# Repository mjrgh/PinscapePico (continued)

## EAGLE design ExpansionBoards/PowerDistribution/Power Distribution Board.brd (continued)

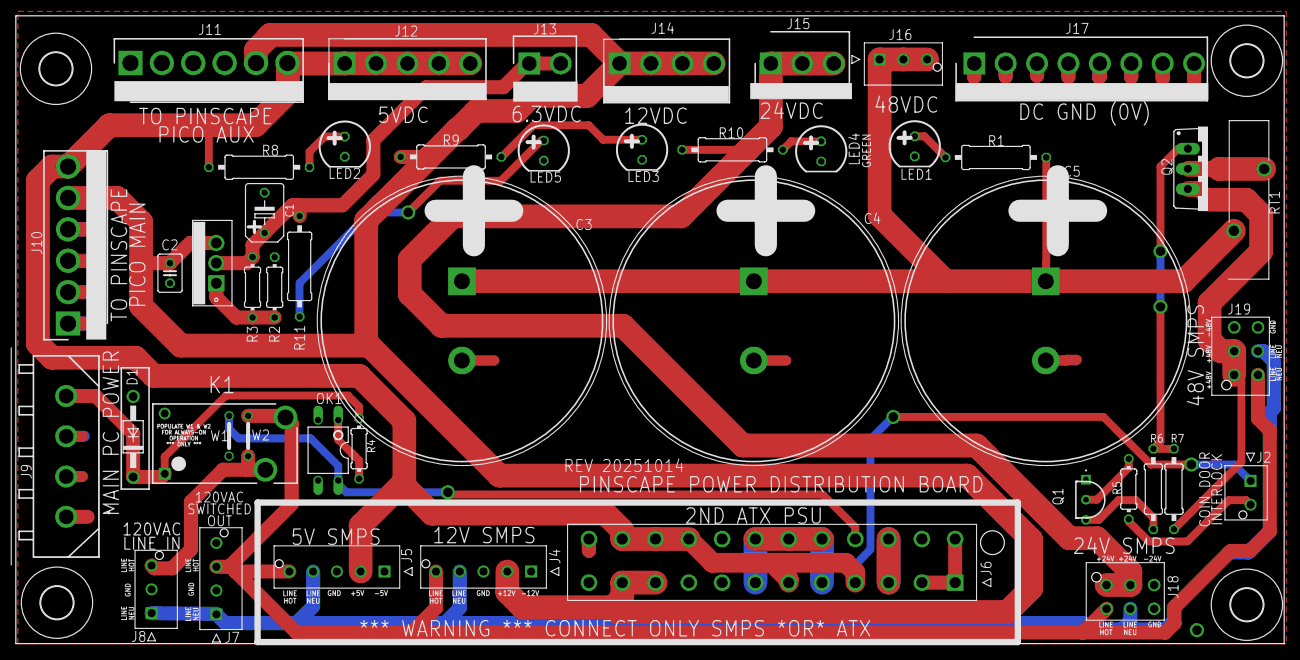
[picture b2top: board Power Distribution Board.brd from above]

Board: 2 copper layers, 160.0 x 79.2 mm, 51 parts (0 on the bottom side), 25 nets.

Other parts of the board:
U$1, U$2, U$3, U$4: 4,1

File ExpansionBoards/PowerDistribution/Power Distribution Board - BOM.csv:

Qty,Value,Parts,Description,PARTNO,Comments,ExtDescription
1,LED 5mm Blue,LED1,"LED, 5mm, blue",C503B-BCN-CV0Z0462,,"LED, 5mm, blue (LED1)"
1,0.1uF,C2,"Capacitor, ceramic, 0.1uF, radial, 2.54mm lead pitch",K104K15X7RF5TL2,,"Capacitor, ceramic, 0.1uF, radial, 2.54mm lead pitch (C2)"
1,1.1K,R2,"Resistor, 1.1K, axial, 2mm x 4mm",MFR-12FTF52-1K1,,"Resistor, 1.1K, axial, 2mm x 4mm (R2)"
1,1uF,C1,"Capacitor, Tantalum, 1uF, radial, 5mm lead pitch",TAP105K035CRS,,"Capacitor, Tantalum, 1uF, radial, 5mm lead pitch (C1)"
1,2.4K/1W,R1,"Resistor, 2.4K, 1W, axial, 3mm x 9mm",279-RR02J2K4TB,,"Resistor, 2.4K, 1W, axial, 3mm x 9mm (R1)"
1,MicroFit Hdr 2P,J2,"Molex Micro-Fit+ vertical header, 2 Ckt, black",538-216571-1002,,"Molex Micro-Fit+ vertical header, 2 Ckt, black (J2)"
1,MicroFit Plug 2P,PLUG_J2,"Molex Micro-Fit+ wire housing, 2 Ckt, black",538-215759-1002,,"Molex Micro-Fit+ wire housing, 2 Ckt, black (PLUG_J2)"
1,MicroFit Hdr 4P,J7,"Molex Micro-Fit+ vertical header, 4 Ckt, black",538-216571-1004,,"Molex Micro-Fit+ vertical header, 4 Ckt, black (J7)"
1,MicroFit Plug 4P,PLUG_J7,"Molex Micro-Fit+ wire housing, 4 Ckt, black",538-215759-1004,,"Molex Micro-Fit+ wire housing, 4 Ckt, black (PLUG_J7)"
1,MicroFit Hdr 3P,J8,"Molex Micro-Fit+ vertical header, 3 Ckt, black",538-216571-2003,,"Molex Micro-Fit+ vertical header, 3 Ckt, black (J8)"
1,MicroFit Plug 3P,PLUG_J8,"Molex Micro-Fit+ wire housing, 3 Ckt, black",538-215759-1003,,"Molex Micro-Fit+ wire housing, 3 Ckt, black (PLUG_J8)"
1,MicroFit Hdr 3P,J16,"Molex Micro-Fit+ vertical header, 3 Ckt, red",538-216571-1023,,"Molex Micro-Fit+ vertical header, 3 Ckt, red (J16)"
1,MicroFit Plug 3P,PLUG_J16,"Molex Micro-Fit+ wire housing, 3 Ckt, red",538-215759-1023,,"Molex Micro-Fit+ wire housing, 3 Ckt, red (PLUG_J16)"
1,MicroFit Hdr 5P,J1,"Molex Micro-Fit+ vertical header, 5 Ckt, black",538-216571-2005,,"Molex Micro-Fit+ vertical header, 5 Ckt, black (J1)"
1,MicroFit Plug 5P,PLUG_J1,"Molex Micro-Fit+ wire housing, 5 Ckt, black",538-215759-1005,,"Molex Micro-Fit+ wire housing, 5 Ckt, black (PLUG_J1)"
1,MicroFit Hdr 5P,J3,"Molex Micro-Fit+ vertical header, 5 Ckt, red",538-216571-1025,,"Molex Micro-Fit+ vertical header, 5 Ckt, red (J3)"
1,MicroFit Plug 5P,PLUG_J3,"Molex Micro-Fit+ wire housing, 5 Ckt, red",538-215759-1025,,"Molex Micro-Fit+ wire housing, 5 Ckt, red (PLUG_J3)"
1,MicroFit Hdr 5P,J4,"Molex Micro-Fit+ vertical header, 5 Ckt, blue",538-216571-1035,,"Molex Micro-Fit+ vertical header, 5 Ckt, blue (J4)"
1,MicroFit Plug 5P,PLUG_J4,"Molex Micro-Fit+ vertical header, 5 Ckt, blue",538-215759-1035,,"Molex Micro-Fit+ vertical header, 5 Ckt, blue (PLUG_J4)"
1,MicroFit Hdr 5P,J5,"Molex Micro-Fit+ vertical header, 5 Ckt, yellow",538-216571-1045,,"Molex Micro-Fit+ vertical header, 5 Ckt, yellow (J5)"
1,MicroFit Plug 5P,PLUG_J5,"Molex Micro-Fit+ vertical header, 5 Ckt, yellow",538-215759-1045,,"Molex Micro-Fit+ vertical header, 5 Ckt, yellow (PLUG_J5)"
35,MicroFit Crimp Pin,,"Molex Micro-Fit+ crimp pins, tin plating, 24-20 AWG",206460-0021,Select according to desired wire gauge,"Molex Micro-Fit+ crimp pins, tin plating, 24-20 AWG ()"
35,MicroFit Crimp Pin,,"Molex Micro-Fit+ crimp pins, tin plating, 18 AWG",206460-0031,Select according to desired wire gauge,"Molex Micro-Fit+ crimp pins, tin plating, 18 AWG ()"
1,Mini-Fit Jr. Hdr 24P,J6,"Molex Mini-Fit Jr. vertical header, 24 Ckt",44206-0007,,"Molex Mini-Fit Jr. vertical header, 24 Ckt (J6)"
1,1N4007,D1,"Diode, general-purpose rectifier, through-hole DO-41 package",1N4007,,"Diode, general-purpose rectifier, through-hole DO-41 package (D1)"
2,270R,"R3, R4","Resistor, 270 Ohm, axial, 2mm x 4mm",CFR25SJT-26-270R,,"Resistor, 270 Ohm, axial, 2mm x 4mm (R3, R4)"
1,350211-1,J9,"Mate-N-Lok PCB header, 4-pos straight (PC ATX floppy disk connector, male)",571-3502111,,"Mate-N-Lok PCB header, 4-pos straight (PC ATX floppy disk connector, male) (J9)"
1,571-6404452,J13,"MTA-156 pin header, 2 position",571-6404452,,"MTA-156 pin header, 2 position (J13)"
1,571-3-643819-2,PLUG_J13,"MTA-156 wire housing, IDC, 2 position, 22AWG",571-3-643819-2,,"MTA-156 wire housing, IDC, 2 position, 22AWG (PLUG_J13)"
1,571-6404453,J15,"MTA-156 pin header, 3 position",571-6404453,,"MTA-156 pin header, 3 position (J15)"
1,571-3-643819-3,PLUG_J15,"MTA-156 wire housing, IDC, 3 position, 22AWG",571-3-643819-3,,"MTA-156 wire housing, IDC, 3 position, 22AWG (PLUG_J15)"
1,571-640445-5,J12,"MTA-156 pin header, 5 position",571-640445-5,,"MTA-156 pin header, 5 position (J12)"
1,571-3-643819-5,PLUG_J12,"MTA-156 wire housing, IDC, 5 position, 22AWG",571-3-643819-5,,"MTA-156 wire housing, IDC, 5 position, 22AWG (PLUG_J12)"
1,571-640445-4,J14,"MTA-156 pin header, 4 position",571-640445-4,,"MTA-156 pin header, 4 position (J14)"
1,571-3-643819-4,PLUG_J14,"MTA-156 wire housing, IDC, 4 position, 22AWG",571-3-643819-4,,"MTA-156 wire housing, IDC, 4 position, 22AWG (PLUG_J14)"
2,571-640445-6,"J10, J11","MTA-156 pin header, 6 position",571-640445-6,,"MTA-156 pin header, 6 position (J10, J11)"
2,571-3-643819-6,"PLUG_J10, PLUG_J11","MTA-156 wire housing, IDC, 6 position, 22 AWG",571-3-643819-6,,"MTA-156 wire housing, IDC, 6 position, 22 AWG (PLUG_J10, PLUG_J11)"
1,571-640445-8,J17,"MTA-156 pin header, 8 position",571-640445-8,,"MTA-156 pin header, 8 position (J17)"
1,571-3-643819-8,PLUG_J17,"MTA-156 wire housing, IDC, 8 position, 22 AWG",571-3-643819-8,,"MTA-156 wire housing, IDC, 8 position, 22 AWG (PLUG_J17)"
1,AHQSS105DM2FA0G,K1,"Relay, 5V coil, 16A switch contacts, contact form A",523-AHQSS105DM2FA0G,,"Relay, 5V coil, 16A switch contacts, contact form A (K1)"
1,LM338T/NOPB,U3,"Voltage regulator, LM338T/NOPB",LM338T/NOPB,,"Voltage regulator, LM338T/NOPB (U3)"
1,SL22_7R010,RT1,"Inrush Current Limiter, 22mm, 7 ohms, 10A",995-SL22-7R010,,"Inrush Current Limiter, 22mm, 7 ohms, 10A (RT1)"
3,B41231B8828M000,"C3, C4, C5","Aluminum Electrolytic Capacitor, 8200uf, 63, Snap-in, 10mm lead spacing",B41231B8828M000,,"Aluminum Electrolytic Capacitor, 8200uf, 63, Snap-in, 10mm lead spacing (C3, C4, C5)"
1,2N2222A,Q1,"NPN Transistor, TO-92, 40V, 600mA, 2N2222A",637-2N2222A,,"NPN Transistor, TO-92, 40V, 600mA, 2N2222A (Q1)"
1,IRF9530,Q2,"MOSFET, P-Channel, TO-220, 100V, 14A, IRF9530",942-IRF9530NPBF,,"MOSFET, P-Channel, TO-220, 100V, 14A, IRF9530 (Q2)"
1,470R,R5,"Resistor, 470 Ohm, axial, 2mm x 4mm",CFR25SJT-52-470R,,"Resistor, 470 Ohm, axial, 2mm x 4mm (R5)"
1,8.2K 1W,R6,"Resistor, 8.2K, 1/4W, axial, 2mm x 7mm",CFR-25JT-52-8K2,,"Resistor, 8.2K, 1/4W, axial, 2mm x 7mm (R6)"
1,2.2K,R7,"Resistor, 2.2K, axial, 2mm x 4mm",CFR25SJT-26-2K2,,"Resistor, 2.2K, axial, 2mm x 4mm (R7)"
1,LTV-817,OK1,Transistor Output Optocoupler,LTV-817-A,,Transistor Output Optocoupler (OK1)
1,LED 5mm Red,LED2,"LED, 5mm, red",C503B-RAN-CZ0C0AA2,,"LED, 5mm, red (LED2)"
1,150R,R8,"Resistor, 150 Ohm, axial, 2mm x 7mm",MFR-25FTF52-150R,,"Resistor, 150 Ohm, axial, 2mm x 7mm (R8)"
1,LED 5mm Yellow,LED3,"LED, 5mm, yellow",151034YS03000,,"LED, 5mm, yellow (LED3)"
1,510R3 1/4W,R9,"Resistor, 510 Ohm, 1/4W, axial, 2mm x 7mm",MFR-25FRF52-510R,,"Resistor, 510 Ohm, 1/4W, axial, 2mm x 7mm (R9)"
1,LED 5mm Green,LED4,"LED, 5mm, green",LTL-4234,,"LED, 5mm, green (LED4)"
1,1.1K 1/2W,R10,"Resistor, 1.1K, 1/2W, axial, 2mm x 7mm",MF0207FTE52-1K1,,"Resistor, 1.1K, 1/2W, axial, 2mm x 7mm (R10)"
1,LED 5mm Orange,LED5,"LED, 5mm, orange",WP7113ED,,"LED, 5mm, orange (LED5)"
1,220R,R11,"Resistor, 220 Ohm, axial, 2mm x 7mm3",MFR50SFTE52-220R,,"Resistor, 220 Ohm, axial, 2mm x 7mm3 (R11)"

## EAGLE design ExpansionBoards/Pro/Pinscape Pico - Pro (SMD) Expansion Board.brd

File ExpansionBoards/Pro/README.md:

# Pinscape Pico "Pro" Expansion Board

This is a set of EAGLE plans for an all-in-one expansion board for
Pinscape Pico.  It includes all of the I/O ports and on-board
peripherals needed for a high-end virtual pinball cabinet, all in a
single board.

I refer to this as the "Pro" board, because it uses small-pitch SMD
parts that make it difficult to assemble by hand.  It's best suited
for robotic assembly, which probably puts it out of reach for DIY
builds.  Factory assembly of a large board like this is usually only
cost-effective when you're making at least 50 to 100 units, so I think
the only people who will want to build this board are our more
entrepreneurially-minded community members who plan to stock a batch
for retail sales.  There's a separate two-board "DIY-Friendly" set,
based entirely on through-hole parts that are easy to solder by hand,
that should be a lot more interesting if you're only planning to build
one for your own use.

## Features

* 32 button inputs, using 74HC165 shift registers for extremely
low latency

* 24 high-power MOSFET outputs with fixed-frequency (98kHz) PWM,
for devices like solenoids, motors, and basic ("dumb") LED strips

* 4 high-power MOSFET outputs with adjustable PWM frequency per port,
for devices that need special PWM frequency settings

* 15 flasher ports, 1 Amp per port, for connecting up to two flasher panels
(with 5 RGB LEDs each) in parallel, using the same ribbon cable connector
as the original Pinscape KL25Z boards; plus a 16th 1A port for a strobe
or other medium-power device

* 8 lamp ports, 500mA per port, for pushbutton lamps or other medium-power devices

* 16 small-LED ports, 120mA per port, for individual low-power LEDs

* Plunger connector compatible with the original Pinscape KL25Z expansion board plunger header,
with software support for all of the same sensors

* IR receiver and transmitter connectors, for connecting a sensor and emitter that can
be positioned anywhere inside or outside the cabinet, for line-of-sight contact
with communicating devices

* Analog input port for a two-axis potentiometer-based joystick or any other ad hoc analog inputs

* UART port for logging and console connections to the Pinscape Pico firmware

* Accelerometer (LIS3DH, but the design can be easily adapted to any other I2C accelerometer)

* High-resolution ADC (ADS1115), for improved plunger sensor input

* Real-time clock chip with con-cell battery backup, for timekeeping while the power is off

* Pinscape TV-ON power detection circuit

* Hard reset button for the Pico

## JLCPCB edition

This board is tailored to the parts catalog for JLCPCB, a Chinese PCB
fabricator that sells direct to hobbyists.  I decided to design the
board around JLCPCB's parts catalog so that I had a concrete vendor
reference point to make sure the board was actually feasible to
manufacture, with parts that could be sourced at the vendor.

There's absolutely no hard dependency on JLCPCB as the manufacturer.
Virtually every fabricator will accept the Gerber files that EAGLE can
mechanically generate from the board layout, and most fabricators can
source whatever parts you specify, one way or another.  It's just likely
to cost more and take longer if your fabricator has to order parts
separately.  If you do want to order the board from another fabricator,
you might want to go through the parts list and substitute parts that
your selected vendor keeps in stock wherever possible.  That might
require some slight customization of the board layout, of course.

## Status

This design is currently a prototype, on paper only.  I haven't
built a physical version of the whole board, although I've
physically build and tested all of the main sub subsystems to
verify that the electronic designs are sound.

All of the devices on this board are supported by the Pinscape Pico
software, and the Config Tool comes with a template configuration
file with all of the necessary settings.

## Design Notes

Some notes on choices I made in the design.

### Component selection

My original goal with the board was hand-assembly, so I started off
trying to use components that are large enough to manipulate by hand
(using tweezers, certainly, but still "by hand" as opposed to "by
robot") and that use solder-pin layouts that are feasible to assemble
with solder paste and a heat gun.  For the passive components like
resistors and capacitors, I instituted a minimum size of "1206" (which
is an electronics industry jargon term meaning 0.12" by 0.6").  I've
found that 1206 is the smallest SMD package that I can comfortably
manipulate with tweezers; it's actually quite large by modern industry
standards, but everything smaller is just too hard to work with, at
least for me.  Similarly, I tried to avoid hidden-pin IC packages like
QFN, and tried to avoid super-fine-pitch ICs below 0.5mm pitch.  Even
0.5mm pitch is tricky to solder, but it's doable with some practice.

This edition of the board doesn't stick to those limits, though.  For
this edition, I specifically targeted factory assembly, which opened
the design to smaller passive parts and other IC packages.  There are
a number of 0402 and 0603 passives, and some QFN ICs.  This allowed
improving the layout, and it also reduces the component cost of the
board, since some of the QFN parts are (for whatever reason)
significantly less costly than their SOIC versions.

### Single-sided component placement

I intentionally placed all of the components on one side of the board.
With SMD components, it's common to place components on both sides of
the board to increase density, but I avoided this because it makes
hand-assembly more difficult and typically increases the cost of
factory assembly.

### Connectors

Most of the connectors are from the TE Connectivity MTA series.  These
connectors have polarized headers, ensuring that the connector is
always inserted in the correct orientation, and the wire housings use
IDC termination with individual wires (not ribbon cables).  I wanted
to give this a try because IDC connectors are a lot quicker to
assemble then crimp-pin connectors, and they're much more reliable
than screw terminals.  I think most DIYers tend to favor screw
terminals because they don't require any special tooling or expertise
to use, but the trade-off is that they're unreliable, at least in my
experience.  I want the wiring inside my pin cab to be very robust; I
don't have to constantly troubleshoot loose connections.  I think IDC
connectors provide the best combination of reliability and quick
assembly.  However, it should be possible to replace the MTA parts
with screw terminals or crimp-pin parts.  There are Molex crimp-pin
products with the same header pin pitch as the corresponding MTA
headers.

For the plunger connector and the RGB flasher output connector, I kept
the same headers, with the same pin layouts, used in the original
Pinscape expansion boards.  This allows anyone upgrading an original
Pinscape system to just plug their existing plunger and flasher cables
into the new boards.  The one change I made vs the original boards is
that I used "shrouded" headers on this board (the original boards had
plain headers without shrouds).  The shrouded header provides a
polarizing key to ensure that the connector is inserted in the correct
orientation.

I also used shrouded 0.1" pitch, two-row pin headers for the button
inputs.  These are best with mating crimp-pin wire housings; I don't
think there are any individual-wire IDC housings available in a
two-row configuration like this, and ribbon cables aren't appropriate
here, so that leaves the crimp-pin headers.  There just isn't room for
32 buttons worth of single-row headers or screw terminals.  If you
really want screw terminals, it would be fairly easy to design a
daughter-board that would plug into the pair of 16-pin button headers,
and route the pins out to screw terminals.

The secondary power supply input is a connector that mates with the
standard floppy-disk connector on an ATX power supply.  This lets you
just plug one of the unused floppy-disk power cables from your
secondary power supply directly into the board, without having to
build the adapter cabling that was necessary with the original
expansion boards.  Hopefully that's a more convenient setup for most
people.

### Button inputs

Button inputs on the original Pinscape boards were wired directly to
GPIO ports, so each button input required one GPIO port.  That was
workable on the KL25Z, which has about 50 exposed GPIO ports, but not
on the Pico, which only exposes 26 ports.  If we could use all of the
ports for button inputs, we'd have just barely enough for the standard
pin cab complement, but that's not possible because the board has to
reserve about 16 ports for its own purposes.  That leaves only 8 ports
that could be assigned as button inputs, which clearly is too few.  We
therefore need additional hardware for the button connections.

The extra hardware used on this board is a set of four 74HC165 shift
register chips.  Each chip provides 8 input ports, so this gives us 32
button inputs total.  These chips work well for button inputs because
the Pico can scan them at extremely high speeds - it can scan the
whole set of inputs every 10 to 20 microseconds, for practically zero
latency reading the inputs.

An earlier version of this board used PCA9555 GPIO expander chips
instead of the shift registers.  The PCA9555's have a couple of nice
features compared to the shift registers: they have pull-up resistors
built in, so they don't need the 32 external resistors required in the
shift register version; and they connect to the Pico via the shared
I2C bus, so they only require one extra GPIO on the Pico (for the
PCA9555 interrupt signal line), whereas the shift register chips
require three dedicated GPIO ports.  But the PCA9555's also have a
major disadvantage, which is that I2C is quite slow.  The button scan
time with the PCA9555's is about one millisecond.  That's fast enough
for most purposes, but for a gaming device like this, it's a negative.
That's why the PCA9555 version of the board also wired four of the
button ports directly to GPIOs, so that you could at least have enough
fast ports to cover the flipper button switches.  But I think it's
nicer to have super fast scanning on all of the input ports, so that
you don't have to worry about which ports go with which buttons, thus
the change to all shift register inputs on this version of the board.

### ADC(Analog-to-Digital Converter)

The board has a dedicated ADC chip for quantizing analog voltage input
from a plunger device.  The Pico has its own on-board ADC, but the
Pico's ADC isn't a very good one; it has low resolution and some known
deficiencies.  The most popular plunger sensor type right now is
probably the linear potentiometer, and those benefit greatly from
high-resolution quantization, so I thought it was worth including a
good ADC in the design.

### PWM chips and MOSFET gate drivers

The PWM controllers on this board are TI's TLC59116F, which are
16-channel I2C chips with open-drain outputs that can sink 120mA per
channel.  Note that the "F" suffix is critical here!  TI also sells a
very similar part without the "F" suffix that has constant-current
outputs.  This board requires the open-drain version.

The TLC59116F replaces the TLC5940NT used in the original Pinscape
boards.  This chip has a couple of advantages.  One is that it has a
standard I2C bus interface for the microcontroller connection, which
only requires two GPIO ports on the Pico and is easier to work with
(from the software's perspective) than the older chip's ad hoc serial
interface.  The other is that it has a much higher PWM frequency than
the older chip, at 97kHz.  The high frequency is useful because it's
well above the human hearing range, which makes the PWM signal
inaudible if a PWM-controlled device transduces the PWM signal to
mechanical vibration.  Some devices, particular motors and large
solenoids, tend to vibrate at the PWM frequency when controlled with
PWM.  If the PWM frequency is in the human hearing range (40Hz to at
most 20kHz, depending on the individual), the vibration manifests as
audible noise.  It can be difficult or impossible to get rid of the
vibration with mechanical treatments, so the only workable solution in
many cases is to increase the PWM frequency above 20kHz, so that the
noise is too high-pitched for humans to hear.  The older TLC5940NT
chips couldn't run at high enough frequencies to get out of the
audible range, but the TLC59116F's native 97kHz frequency is safely
out of human range.  It's probably even high enough that it won't
annoy your dog.

The MOSFET outputs are connected to the PWM chips through TI's
UCC27523 gate driver chips.  The UCC27523 is an inverting gate driver
with an internal pull-up, which means that an unconnected or floating
input is pulled high (by the internal resistor) and places the MOSFET
in an OFF state, whereas an input line that's pulled to ground places
the MOSFET in an ON state.  This mates perfectly with the TLC59116F's
open-drain outputs, which are floating when the PWM signal is OFF and
pulled to ground when the PWM signal is ON.  On the MOSFET side, the
UCC27523 provides a high-current push-pull input to the MOSFET gate,
which rapidly charges or discharges the gate at each state change.
The chips are capable of driving the gate at up to 1A, which lets them
charge and discharge high-gate-capacitance MOSFETs at high switching
speeds.  The board uses 12V for the gate drive power supply, which is
compatible with most power MOSFETs in the voltage/current range we
need.  This allows for a very wide range of MOSFETs to be used, since
we don't have to be at all picky about Vgs(th) or gate capacitance.
Board builders can choose MOSFETs based largely on price; just filter
by your minimum Vds and Id needs.

The gate driver chips have the additional benefit that they're
designed for glitch-free startup, which should prevent the annoying
random solenoid firing that sometimes happened with the original
Pinscape boards.

The original Pinscape boards used optocouplers to serve the same
function of inverting the PWM signal to drive the MOSFET gates.  The
UCC27523 chips are a far superior solution, for several reasons.  The
first is that most optocouplers can't switch fast enough to keep up
with the TLC59116F's 97kHz PWM signal, so intensity adjustments
wouldn't pass through reliably to attached devices.  The second is
that optocouplers can't deliver enough current to the MOSFET gate for
efficient switching, which means the MOSFET can heat excessively
because it's spending too much time in a high-resistance state.  Many
larger power MOSFETs have a relatively high gate capacitance that
requires high current on the gate drive to achieve fast enough
switching to avoid excess heating.  The gate driver chips are
specifically designed to deliver high current to the gate for cool
operation.  A bonus feature is that the gate driver chips take up less
space on the board than most optocouplers, which made it possible to
pack more MOSFET output ports onto the board.

### Glitch-free and lockup-free output design

The design has several elements meant to guarantee that the output
ports are free of startup and shutdown glitches (meaning that all of
the output ports consistently OFF when the board is powered on, and
turn off again immediately while the board is being powered down).  I
also tried to ensure that ports designated as solenoid ports can never
lock on due to a software fault, on either the PC or in the Pico
firmware.

Glitch-free startup and shutdown are the hardware's responsibility.
The whole issue here is that there's a brief period at each end of a
power cycle where the software isn't running, because the MCU is
deliberately not executing any software instructions while the voltage
supply is rising or falling.  During these periods, the software can't
send commands to the output controller chips to tell them to disable
the outputs, so the hardware has to be designed in such a way that
everything is deterministically in an OFF state at power-on and again
whenever the MCU is in a reset state.

The TLC59116 chips provide guaranteed glitch-free startup and shutdown
at their output ports (they use an internal power-on reset circuit
that holds the outputs in the OFF state while the supply voltage is
below a threshold).  The small LEDs are directly connected to the
TLC59116 outputs, so those get glitch-free startup by virtue of the
TLC59116's glitch-free startup.  The Darlington outputs and MOSFET
outputs are all triggered through inverters with pulled-up inputs, so
they'll remain OFF whenever their TLC59116 ports are OFF.

Guaranteeing that ports won't lock up due to a software fault is a
separate matter.  Power-on glitching is annoying but rarely does any
damage; locked-up outputs can actually break things.  Pinball coils
such as knockers, and similar large solenoids, are designed for brief
activation only, and will overheat and fail (the coil wire will act
like a fuse and simply melt) if power is applied continuously for more
than a few seconds at a time.  There are two scenarios in a virtual
pinball setup where software faults can leave ports locked on.  The
first is that the application software on the PC crashes or freezes,
or is simply programmed incorrectly, in such a way that it turns an
output port ON and then fails to turn it back OFF soon enough to avoid
damage to the connected device.  USB disconnects and glitches are in
this same class of failures, in that they could prevent the PC from
sending a required OFF command.  The second failure mode is that the
MCU firmware crashes or freezes, which makes it stop responding to
commands from the PC.  If a port is ON at the moment of a crash, the
crashed MCU firmware won't be able to obey the OFF command from the
PC, even if everything on the PC side is still working properly.

The original Pinscape boards took a very hardware-centric approach to
this problem, by providing hardware timers on certain ports (the
knocker port on the main board and all ports on the Chime board).  The
hardware timers were designed so that the port was actually
"edge-sensitive" rather than "level-sensitive": the port only turned
on at a low-to-high transition from the MCU output, and then only
turned on for a fixed time period.  So if the MCU turned a port ON and
then held it on continuously, the timed port would only stay on for
the hardware-programmed interval, and wouldn't turn on again until a
new low-to-high transition on the MCU port.  This approach inherently
addressed every possible software fault up and down the entire
software stack, because the only thing that mattered was the final
port signal coming out of the MCU.  If the final port signal got stuck
ON, for whatever reason, the port would still turn off thanks to the
hardware timer.

This design doesn't have the hardware timers.  They add a lot of
complexity and extra parts, and I decided we could get the same level
of reliability without them.  The hardware timers also weren't
configurable - a port was either a timer-protected port or it wasn't.
Doing everything in software lets you designate any port for timer
protection, and also allows for variations on the behavior, such as
adjusting the timer interval, and having the option to switch a port
to a low-power mode after the timeout (the "flipper logic" scheme in
the original Pinscape software) instead of cutting power entirely.

The new design has three layers of protection.  These are truly
layers, in that each one is an independent backup for the next.  The
first layer is the Flipper Logic/Chime Logic software control, which
applies the same principle as the original hardware timer, but
implemented in the firmware software instead of in dedicated hardware
on the board.  This is the weakest link in terms of the "guarantee",
since it depends upon the firmware correctly executing the timer
behavior as configured.  My own estimation is that the timer logic
itself is simple enough that it can be made highly reliable IN
ISOLATION - meaning that we can rely on it to function properly AS
LONG AS the firmware OVERALL is still running properly.  The main
risk, in other words, isn't that the timer logic would screw up, but
that a bug in some unrelated part of the software would cause the
whole firmware program to crash or freeze or get stuck doing some
unrelated task, preventing the part of the code that operates the
timer from executing properly or in a timely fashion.

That's where the second layer of protection comes in.  The second
layer is the Pico's "watchdog".  This is a hardware subsystem on the
Pico that runs a hardware countdown timer that reboots the Pico after
a software-configured interval expires, UNLESS the software intervenes
to prevent the reboot.  This is a widely used technique in embedded
systems, and it's highly effective, because it provides a
hardware-level guarantee that the system will reset if the software
doesn't behave "as expected", where the expectation is that the
software must, in essence, tell the watchdog "I'm still working" at
regular intervals.  For this application, the interval in question
simply has to be shorter than the time it would take for lock-up
condition to damage an attached pinball coil.  This is within entirely
reasonable bounds - it takes a couple of seconds of lock-up to burn
out most coils, and the firmware main loop is on the order of
milliseconds.  So setting the watchdog interval to something on the
order of 10 to 100 milliseconds would catch lock-ups well before they
could do any damage.  It's still important to design the software
carefully; in particular, since the most important purpose of the
watchdog by far is to prevent output port lock-up, the watchdog "I'm
still alive" signaling should be closely coupled to the code that
executes the port protection timers.

The third layer of protection is similar to the power-on glitch
protection, but in this case it applies to the MCU RESET condition
rather than power supply transitions.  This layer is necessarily at
the hardware level, since it has to deal with the aftermath of a
software fault that caused the Pico watchdog to intervene by resetting
the Pico.  The goal here is to ensure that all of the output ports are
immediately and deterministically turned OFF when the Pico enters
RESET state, and deterministically stay off until the software
restarts and takes control of the ports again.  We can accomplish this
fairly easily by taking advantage of a hardware feature of the Pico,
and a hardware feature of the TLC59116 chips.  When the Pico is in the
RESET state, it configures all of its GPIO ports as "inputs", which
places them in a high-impedance state (essentially an open-drain
connection).  The input/high-impedance configuration remains in effect
until the software explicitly changes the GPIO to some other mode, so
this is the state from the moment a RESET occurs until the software is
fully in control again.  So let's start by designating one Pico GPIO
as the /OUTPUT_RESET signal, and tying this GPIO to GND through a
pull-down resistor.  The pull-down assures that this signal will be at
GND through a Pico reset, and remain at GND until the software
explicitly programs the port as an output and drives it high.  We can
then tie this /OUTPUT_RESET signal to the /RESET input pin on each of
the TLC59116 chips.  Holding this line low on a TLC59116 forces all of
the chip's output ports to their OFF state, exactly as during the
power-on/power-off supply voltage transitions.  This ensures that the
connected small LED, Darlington, and MOSFET ports are all off, for the
reasons discussed above.  When the CPU completes its RESET cycling, it
will restart the firmware, which will in turn initialize its
connections to the TLC59116 chips.  Part of this initialization will
be to drive the /OUTPUT_RESET line high to allow the TLC59116 chips to
come out of their reset state.  When they do, they're designed to hold
all of the outputs OFF until the host explicitly sets them to another
state, so we have a smooth transition back into normal operation, with
all ports turned OFF and held OFF until the software is properly
running again.

### Darlington outputs and small LED outputs

Like the original Pinscape boards, this board has a mix of MOSFET
outputs, Darlington outputs, and direct PWM-chip outputs.  All of the
ports work the same way from the user's perspective: they're all
low-side switches that serve as the "ground" connection for one device
each.  The only difference between the port types is the amount of
power that each port can handle.  Ideally, every port would be a
MOSFET port, because those are the most general-purpose port, capable
of handling any type of device from low power to high power.  Cab
builders wouldn't have to worry about using special port types per
device because every port would work with any device.  The reason we
*didn't* use all MOSFET ports is that it would take up too much space
on the board.  A MOSFET port takes up about twice the amount of space
of a Darlington port, which in turn takes up perhaps 4X the space of a
small LED port.  The mixture of port types makes it possible to
include enough ports to connect all of the common virtual pinball
devices without making the circuit board gigantic (and prohibitively
expensive).

The theory of operation of the MOSFET ports was described earlier.
The Darlington ports work similarly, but Darlingtons don't need the
gate driver chips, since they trigger on a small current on the
transistor base.  Instead, we use a small pre-biased PNP transistor on
each port to act as a logic inverter to convert the TLC59116F's
open-drain output logic to a positive voltage source on the Darlington
base input.  The Pinscape boards used optocouplers to serve the same
purpose for their Darlington outputs; the PNP inverters in this design
take up less space and switch faster than typical optocouplers, which
(as mentioned in the MOSFET section above) is necessary to handle the
TLC59116F's high PWM frequency.  The pre-biased PNP transistors are
available in "array" packages that have two transistor (and the
associated bias transistors) per package, which further improves board
density and assembly workload.

The direct PWM output ports for small LEDs work almost exactly the
same way as in the original Pinscape board.  These output ports on the
board are simply wired directly to the corresponding TLC59116F ports,
without any booster circuitry, which means they can sink up to the
maximum current that the TLC59116F chip itself can handle, which is
120mA per port (which is ample for virtually any small LED).  The only
difference from the original Pinscape boards is that these chips are
simple open-drain current sinks, whereas the original boards had
constant-current sinks.  On this board, therefore, the external LED
circuit must include a current-limiting resistor.  I think this is an
improvement over the constant-current ports on the original Pinscape
boards, since it's much easier to use with a heterogeneous set of
LEDs.  The constant-current sink on the original boards was convenient
in that you didn't need to include current-limiting resistors, but the
requirement to choose a fixed current level was too inflexible.

### IR Remote

This board has support for an optional IR remote control transmitter
and receiver.  You can connect either or both as desired.  The IR
transmitter lets you send commands to your TVs and any other devices
that can receive IR signals, which you can use to send them commands
to power on, select inputs or video modes, etc.  The IR receiver lets
Pinscape receive IR remote control codes from just about any IR remote
control you have handy.  You can use IR remote inputs as though they
were physical buttons on the cabinet, to send commands to the PC host.

Both the transmitter and receiver are designed to be separated from
the main board, so that you can place them in convenient locations
where transmitters and receivers can "see" each other properly.  This
lets the signals get in and out even if the main board is buried deep
inside your pinball cabinet.  The off-board devices connect to
the main board through cables, which connect to headers on the main
board (the headers labeled IR-TX, for the transmitter, and IR-RX, for
the receiver).

<b>Transmitter:</b>  The IR transmitter is located off of the main
board, but it doesn't require its own separate circuit board, because
the whole receiver consists of just a single small LED.  You simply
solder wires directly to the LED and run them back to the main
board.  See the [IR-TX](../IR-TX/) folder for help with wiring the IR LED.
After wiring the LED, plug it into the IR-TX header on the main board.

Note that the BOM lists two options for the IR LED: VSLB4940 and
TSAL6400.  You only need one or the other, and they're
interchangeable, so you can pick whichever one is cheaper or more
readily available.  No changes are required to the expansion board.
Other things being equal, I'd go with VSLB4940, because it has
slightly better luminosity specs, which should give it slightly better
range.

<b>Receiver:</b> The receiver requires a small "satellite" circuit
board, because the sensor that does the receiving has a couple of
extra supporting parts that have to be installed alongside it.  See the
[IR-RX](../IR-RX/) folder for the receiver circuit board design.  After building the
board and wiring the cable, plug the cable into the IR-RX header on
the main board.

### Power sensing circuit

This board uses a redesigned power-sensing circuit.  It serves the
same function as the power-sensing circuit on the original Pinscape
boards, and has a similar theory of operation, but I revamped the
electronic design using a couple of special-purpose IC chips rather
than the discrete component design of the original boards.

The original circuit is essentially a flip-flop that resets to a logic
'0' state each time the secondary power supply (PSU2) powers up.  The
microcontroller (KL25Z on the old board, Pico on the new board) reads
the flip-flop state through an optocoupler, which isolates the MCU's
power supply from the secondary supply.  The isolation is critical
because the whole point of the circuit is to let the MCU detect when
power has been cycled on the secondary supply even if the MCU itself
is continuously powered at all times through the USB port, which is
usually the case due to the PC being on a "soft power" control rather
than actually having its AC power cord unplugged between sessions.
The MCU can also attempt to *set* the flip-flop state through a second
optocoupler.  When the flip-reads as logic '0', it means that either
PSU2 is off (so it can't power the optocoupler, causing it to read as
a zero voltage and thus logic '0') *or* that the flip-flop has been
reset (cleared to logic '0') by a power cycle on PSU2 (recall that the
circuit is designed so that the flip-flop is always cleared after a
power cycle).  The MCU can distinguish the two cases by attempting to
set the flip-flop, and then reading back the result; if the flip-flop
reads as logic '1' after the set operation, the flip-flop must have
power, so the fact that it read as '0' previously means that PSU2 has
been turned back on after a period of being off.  This state change is
what triggers the TV-ON timer because it means that the cab has just
been powered up and is in the process of initializing.  If the
flip-flop still reads as '0' after a set operation, it means that PSU2
is currently off, so the MCU should do nothing for now and simply
check back later.

The old design used a couple of transistors to implement the
flip-flop.  The new design uses a flip-flop IC instead.  Since
flip-flop ICs power on in an indeterminate state, we also use a "POR"
(Power-On Reset) IC to force the flip-flop into a logic '0' state when
PSU2 powers on.  The POR chip is a special-purpose chip designed to
assert a RESET signal for a predictable interval after the power
supply stabilizes above a threshold voltage after being below the
threshold (typically meaning that power was off for a time).  The
combination of the flip-flop and POR chip (plus the pair of
optocouplers from the original design) implements exactly the behavior
we need.  The reason for the redesign is that it uses fewer
components, reducing cost and assembly workload, and accomplishes the
design goals more robustly.  The flip-flop and POR chips are designed
for these specific tasks, and are engineered to much higher standards
than my ad hoc design.

### 6.3VDC power supply

An early version of the board included a 6.3V regulator to supply
power for commonly used small pinball lamps (#555, #44, etc), used in
coin doors (for the coin chute lamps) and Suzo-Happ lighted
push-buttons.  This was eliminated in later versions (due to space
constraints).  However, there's a companion Power Distribution Board
that includes the same 6.3V regulator.

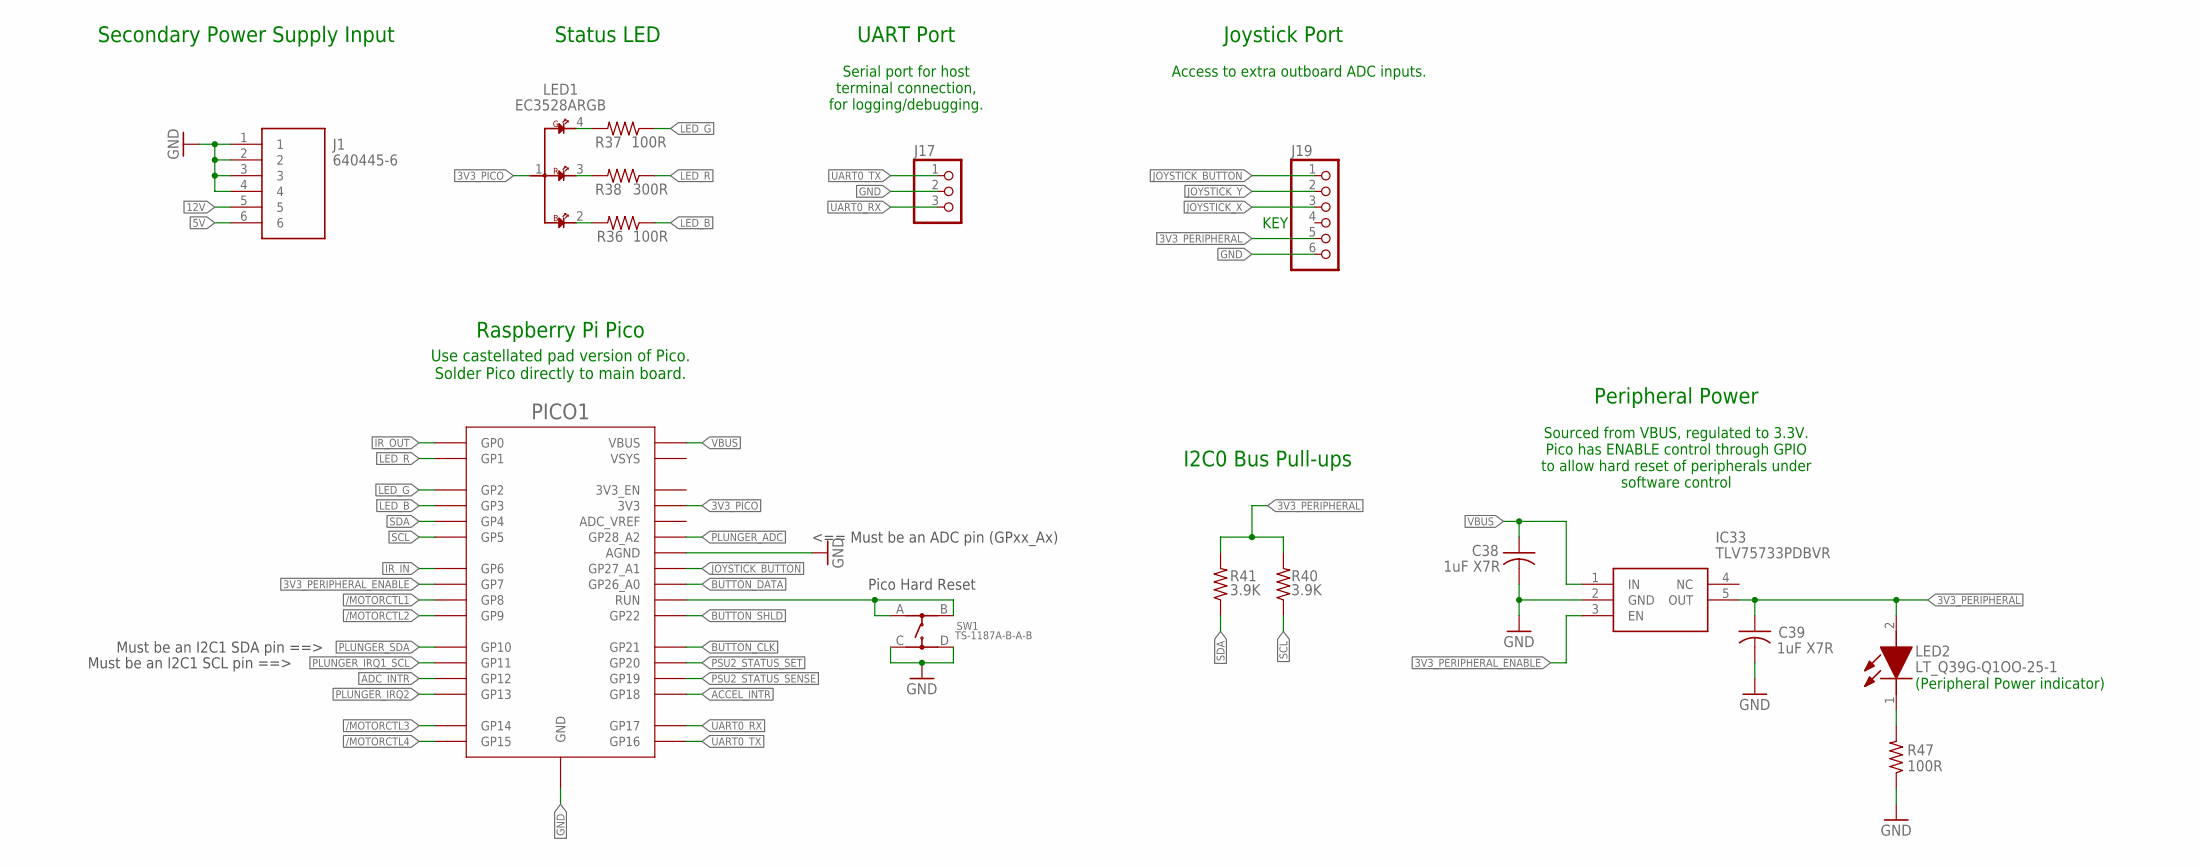
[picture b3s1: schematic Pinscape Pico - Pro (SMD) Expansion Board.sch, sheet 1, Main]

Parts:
C38, C39: 1uF X7R; C1206
IC33: TLV75733PDBVR; SOT95P280X145-5N
J1: 640445-6; SHDR6W183P0X396_1X6_2377X762X1
J17: PINHD-1X3; 1X03
J19: PINHD-1X6; 1X06
LED1: EC3528ARGB
LED2: LT_Q39G-Q1OO-25-1; LEDC1608X40N
PICO1: PICO; RPI_PICO_TH_NO_DEBUG
R36, R37, R47: 100R; R0402
R38: 300R; R0402
R40, R41: 3.9K; R0603
SW1: TS-1187A-B-A-B

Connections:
3V3_PERIPHERAL: C39.1, IC33.5 (OUT), J19.5, LED2.2 (A), R40.2, R41.2; also elsewhere on the board
3V3_PERIPHERAL_ENABLE: IC33.3 (EN), PICO1.GP7
3V3_PICO: LED1.1, PICO1.3V3; also elsewhere on the board
5V: J1.6; also elsewhere on the board
12V: J1.5; also elsewhere on the board
/MOTORCTL1: PICO1.GP8; also elsewhere on the board
/MOTORCTL2: PICO1.GP9; also elsewhere on the board
/MOTORCTL3: PICO1.GP14; also elsewhere on the board
/MOTORCTL4: PICO1.GP15; also elsewhere on the board
ACCEL_INTR: PICO1.GP18; also elsewhere on the board
ADC_INTR: PICO1.GP12; also elsewhere on the board
BUTTON_CLK: PICO1.GP21; also elsewhere on the board
BUTTON_DATA: PICO1.GP26_A0; also elsewhere on the board
BUTTON_SHLD: PICO1.GP22; also elsewhere on the board
GND: C38.2, C39.2, IC33.2 (GND), J1.1, J1.2, J1.3, J1.4, J17.2, J19.6, PICO1.AGND, PICO1.GND@1 (GND), PICO1.GND@2 (GND), PICO1.GND@3 (GND), PICO1.GND@4 (GND), PICO1.GND@6 (GND), PICO1.GND@7 (GND), PICO1.GND@8 (GND), R47.1, SW1.C, SW1.D; also elsewhere on the board
IR_IN: PICO1.GP6; also elsewhere on the board
IR_OUT: PICO1.GP0; also elsewhere on the board
JOYSTICK_BUTTON: J19.1, PICO1.GP27_A1
JOYSTICK_X: J19.3; also elsewhere on the board
JOYSTICK_Y: J19.2; also elsewhere on the board
LED_B: PICO1.GP3, R36.1
LED_G: PICO1.GP2, R37.1
LED_R: PICO1.GP1, R38.1
unnamed: LED1.3, R38.2
unnamed: LED1.2, R36.2
unnamed: LED1.4, R37.2
unnamed: PICO1.RUN, SW1.A, SW1.B
unnamed: LED2.1 (K), R47.2
PLUNGER_ADC: PICO1.GP28_A2; also elsewhere on the board
PLUNGER_IRQ1_SCL: PICO1.GP11; also elsewhere on the board
PLUNGER_IRQ2: PICO1.GP13; also elsewhere on the board
PLUNGER_SDA: PICO1.GP10; also elsewhere on the board
PSU2_STATUS_SENSE: PICO1.GP19; also elsewhere on the board
PSU2_STATUS_SET: PICO1.GP20; also elsewhere on the board
SCL: PICO1.GP5, R40.1; also elsewhere on the board
SDA: PICO1.GP4, R41.1; also elsewhere on the board
UART0_RX: J17.3, PICO1.GP17
UART0_TX: J17.1, PICO1.GP16
VBUS: C38.1, IC33.1 (IN), PICO1.VBUS

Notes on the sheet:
Secondary Power Supply Input
I2C0 Bus Pull-ups
Status LED
Raspberry Pi Pico
Use castellated pad version of Pico. Solder Pico directly to main board.
Must be an I2C1 SCL pin ==>
<== Must be an ADC pin (GPxx_Ax)
Must be an I2C1 SDA pin ==>
Pico Hard Reset
UART Port
Serial port for host terminal connection, for logging/debugging.
Joystick Port
Access to extra outboard ADC inputs.
KEY
Peripheral Power
Sourced from VBUS, regulated to 3.3V. Pico has ENABLE control through GPIO to allow hard reset of peripherals under software control
(Peripheral Power indicator)

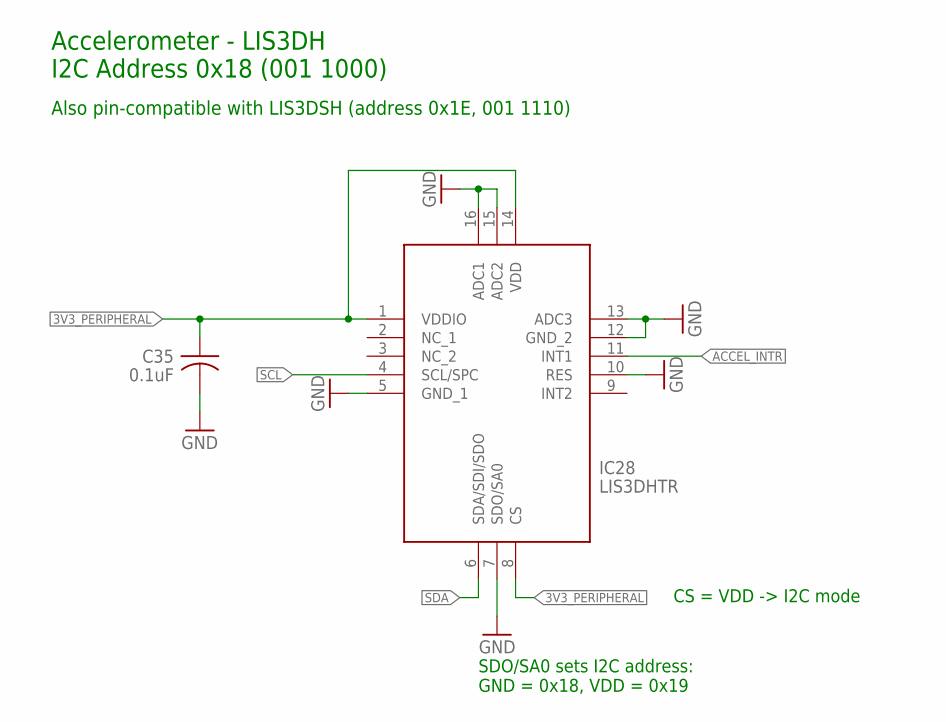
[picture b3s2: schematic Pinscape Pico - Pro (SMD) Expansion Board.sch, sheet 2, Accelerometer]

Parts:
C35: 0.1uF; C0402
IC28: LIS3DHTR

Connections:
3V3_PERIPHERAL: C35.1, IC28.1 (VDDIO), IC28.8 (CS), IC28.14 (VDD); also elsewhere on the board
ACCEL_INTR: IC28.11 (INT1); also elsewhere on the board
GND: C35.2, IC28.5 (GND_1), IC28.7 (SDO/SA0), IC28.10 (RES), IC28.12 (GND_2), IC28.13 (ADC3), IC28.15 (ADC2), IC28.16 (ADC1); also elsewhere on the board
SCL: IC28.4 (SCL/SPC); also elsewhere on the board
SDA: IC28.6 (SDA/SDI/SDO); also elsewhere on the board

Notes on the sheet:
Accelerometer - LIS3DH I2C Address 0x18 (001 1000)
SDO/SA0 sets I2C address: GND = 0x18, VDD = 0x19
CS = VDD -> I2C mode
Also pin-compatible with LIS3DSH (address 0x1E, 001 1110)

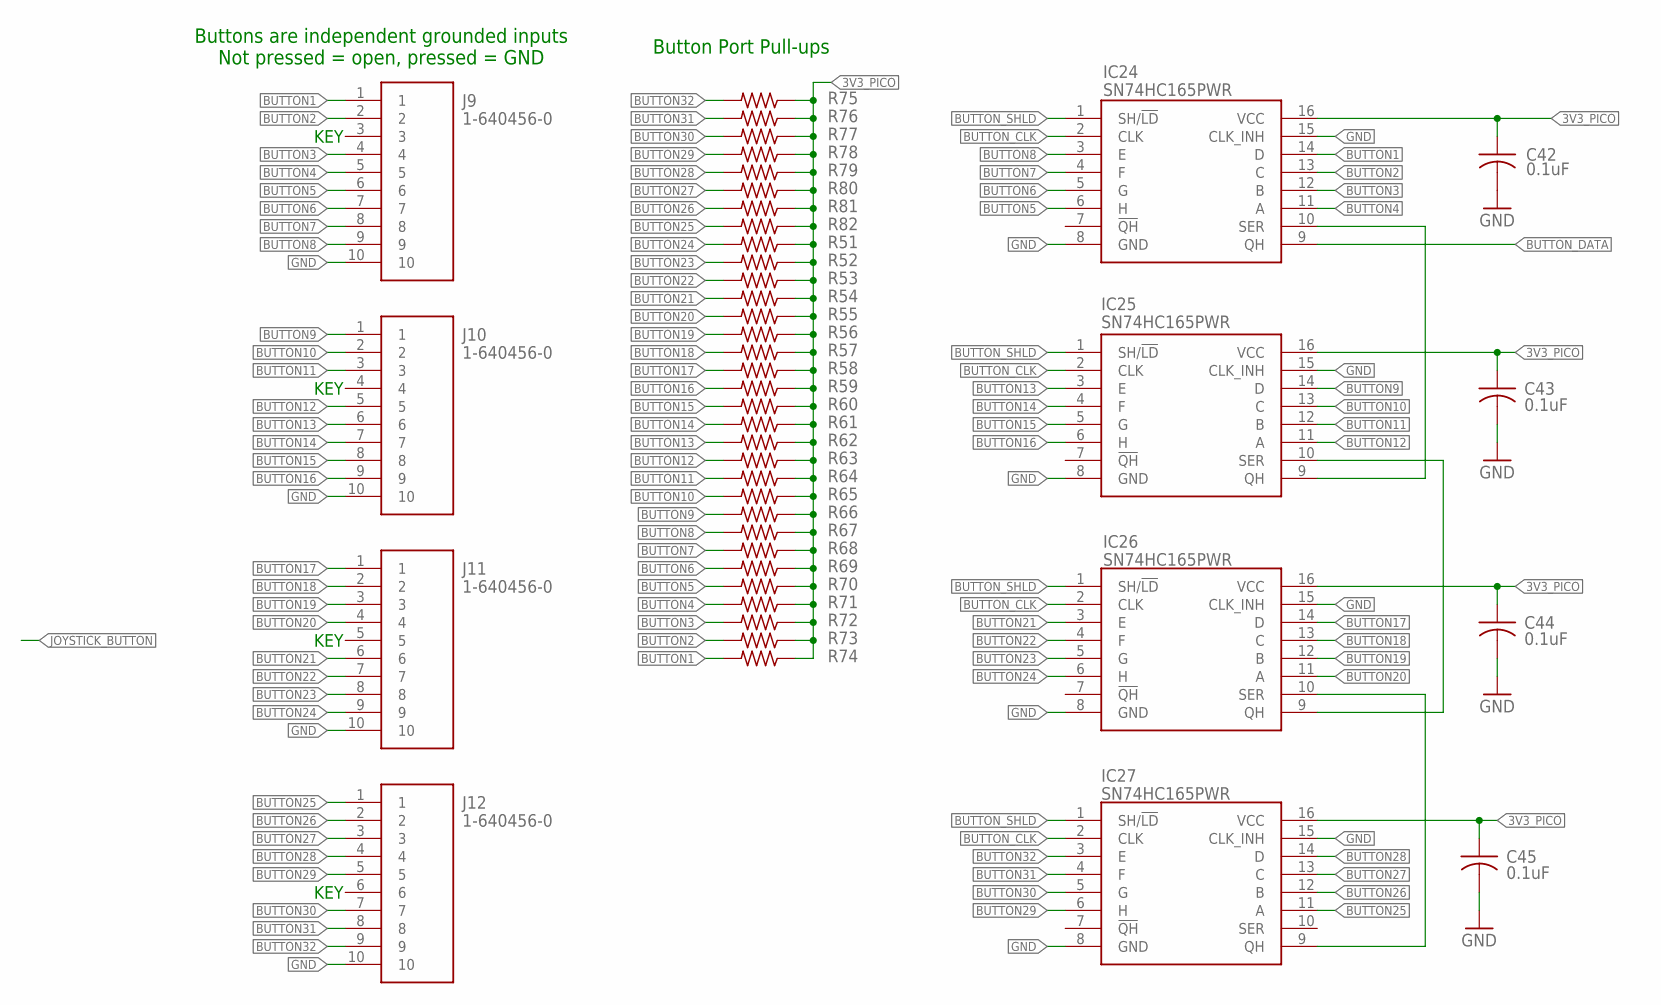
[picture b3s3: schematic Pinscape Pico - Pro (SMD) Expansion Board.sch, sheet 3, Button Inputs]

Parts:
C42, C43, C44, C45: 0.1uF; C0402
IC24, IC25, IC26, IC27: SN74HC165PWR; SOP65P640X120-16N
J9, J10, J11, J12: 1-640456-0; SHDR10W66P0X254_1X10_2540X572X
R51, R52, R53, R54, R55, R56, R57, R58, R59, R60, R61, R62, R63, R64, R65, R66, R67, R68, R69, R70, R71, R72, R73, R74, R75, R76, R77, R78, R79, R80, R81, R82: 10k; R0402

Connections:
3V3_PICO: C42.1, C43.1, C44.1, C45.1, IC24.16 (VCC), IC25.16 (VCC), IC26.16 (VCC), IC27.16 (VCC), R51.1, R52.1, R53.1, R54.1, R55.1, R56.1, R57.1, R58.1, R59.1, R60.1, R61.1, R62.1, R63.1, R64.1, R65.1, R66.1, R67.1, R68.1, R69.1, R70.1, R71.1, R72.1, R73.1, R74.1, R75.1, R76.1, R77.1, R78.1, R79.1, R80.1, R81.1, R82.1; also elsewhere on the board
BUTTON1: IC24.14 (D), J9.1, R74.2
BUTTON2: IC24.13 (C), J9.2, R73.2
BUTTON3: IC24.12 (B), J9.4, R72.2
BUTTON4: IC24.11 (A), J9.5, R71.2
BUTTON5: IC24.6 (H), J9.6, R70.2
BUTTON6: IC24.5 (G), J9.7, R69.2
BUTTON7: IC24.4 (F), J9.8, R68.2
BUTTON8: IC24.3 (E), J9.9, R67.2
BUTTON9: IC25.14 (D), J10.1, R66.2
BUTTON10: IC25.13 (C), J10.2, R65.2
BUTTON11: IC25.12 (B), J10.3, R64.2
BUTTON12: IC25.11 (A), J10.5, R63.2
BUTTON13: IC25.3 (E), J10.6, R62.2
BUTTON14: IC25.4 (F), J10.7, R61.2
BUTTON15: IC25.5 (G), J10.8, R60.2
BUTTON16: IC25.6 (H), J10.9, R59.2
BUTTON17: IC26.14 (D), J11.1, R58.2
BUTTON18: IC26.13 (C), J11.2, R57.2
BUTTON19: IC26.12 (B), J11.3, R56.2
BUTTON20: IC26.11 (A), J11.4, R55.2
BUTTON21: IC26.3 (E), J11.6, R54.2
BUTTON22: IC26.4 (F), J11.7, R53.2
BUTTON23: IC26.5 (G), J11.8, R52.2
BUTTON24: IC26.6 (H), J11.9, R51.2
BUTTON25: IC27.11 (A), J12.1, R82.2
BUTTON26: IC27.12 (B), J12.2, R81.2
BUTTON27: IC27.13 (C), J12.3, R80.2
BUTTON28: IC27.14 (D), J12.4, R79.2
BUTTON29: IC27.6 (H), J12.5, R78.2
BUTTON30: IC27.5 (G), J12.7, R77.2
BUTTON31: IC27.4 (F), J12.8, R76.2
BUTTON32: IC27.3 (E), J12.9, R75.2
BUTTON_CLK: IC24.2 (CLK), IC25.2 (CLK), IC26.2 (CLK), IC27.2 (CLK); also elsewhere on the board
BUTTON_DATA: IC24.9 (QH); also elsewhere on the board
BUTTON_SHLD: IC24.1 (SH/!LD), IC25.1 (SH/!LD), IC26.1 (SH/!LD), IC27.1 (SH/!LD); also elsewhere on the board
GND: C42.2, C43.2, C44.2, C45.2, IC24.8 (GND), IC24.15 (CLK_INH), IC25.8 (GND), IC25.15 (CLK_INH), IC26.8 (GND), IC26.15 (CLK_INH), IC27.8 (GND), IC27.15 (CLK_INH), J9.10, J10.10, J11.10, J12.10; also elsewhere on the board
unnamed: IC25.10 (SER), IC26.9 (QH)
unnamed: IC24.10 (SER), IC25.9 (QH)
unnamed: IC26.10 (SER), IC27.9 (QH)

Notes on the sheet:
Buttons are independent grounded inputs Not pressed = open, pressed = GND
KEY
Button Port Pull-ups

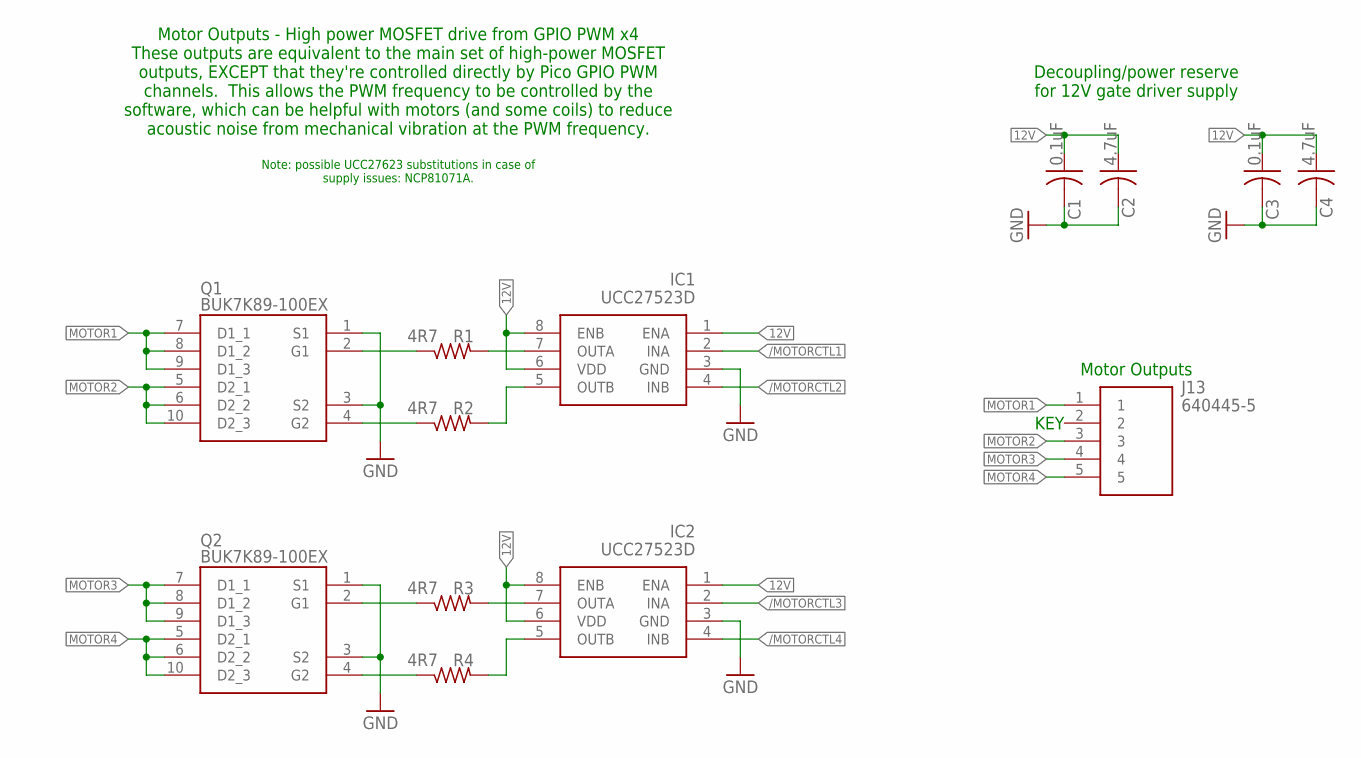
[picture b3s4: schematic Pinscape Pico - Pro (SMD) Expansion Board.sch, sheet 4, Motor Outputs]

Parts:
C1, C3: 0.1uF; C0402
C2, C4: 4.7uF; C1206
IC1, IC2: UCC27523D; SOIC127P600X175-8N
J13: 640445-5; HDRV5W117P0X396_1X5_1981X762X1
Q1, Q2: BUK7K89-100EX; BUK7K89100EX
R1, R2, R3, R4: 4R7; R0603

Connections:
12V: C1.1, C2.1, C3.1, C4.1, IC1.1 (ENA), IC1.6 (VDD), IC1.8 (ENB), IC2.1 (ENA), IC2.6 (VDD), IC2.8 (ENB); also elsewhere on the board
/MOTORCTL1: IC1.2 (INA); also elsewhere on the board
/MOTORCTL2: IC1.4 (INB); also elsewhere on the board
/MOTORCTL3: IC2.2 (INA); also elsewhere on the board
/MOTORCTL4: IC2.4 (INB); also elsewhere on the board
GND: C1.2, C2.2, C3.2, C4.2, IC1.3 (GND), IC2.3 (GND), Q1.1 (S1), Q1.3 (S2), Q2.1 (S1), Q2.3 (S2); also elsewhere on the board
MOTOR1: J13.1, Q1.7 (D1_1), Q1.8 (D1_2), Q1.9 (D1_3)
MOTOR2: J13.3, Q1.5 (D2_1), Q1.6 (D2_2), Q1.10 (D2_3)
MOTOR3: J13.4, Q2.7 (D1_1), Q2.8 (D1_2), Q2.9 (D1_3)
MOTOR4: J13.5, Q2.5 (D2_1), Q2.6 (D2_2), Q2.10 (D2_3)
unnamed: IC1.5 (OUTB), R2.2
unnamed: IC2.5 (OUTB), R4.2
unnamed: IC2.7 (OUTA), R3.2
unnamed: IC1.7 (OUTA), R1.2
unnamed: Q1.2 (G1), R1.1
unnamed: Q1.4 (G2), R2.1
unnamed: Q2.2 (G1), R3.1
unnamed: Q2.4 (G2), R4.1

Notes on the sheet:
Decoupling/power reserve for 12V gate driver supply
Motor Outputs - High power MOSFET drive from GPIO PWM x4 These outputs are equivalent to the main set of high-power MOSFET outputs, EXCEPT that they're controlled directly by Pico GPIO PWM channels. This allows the PWM frequency to be controlled by the software, which can be helpful with motors (an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
Note: possible UCC27623 substitutions in case of supply issues: NCP81071A.
Motor Outputs
KEY
